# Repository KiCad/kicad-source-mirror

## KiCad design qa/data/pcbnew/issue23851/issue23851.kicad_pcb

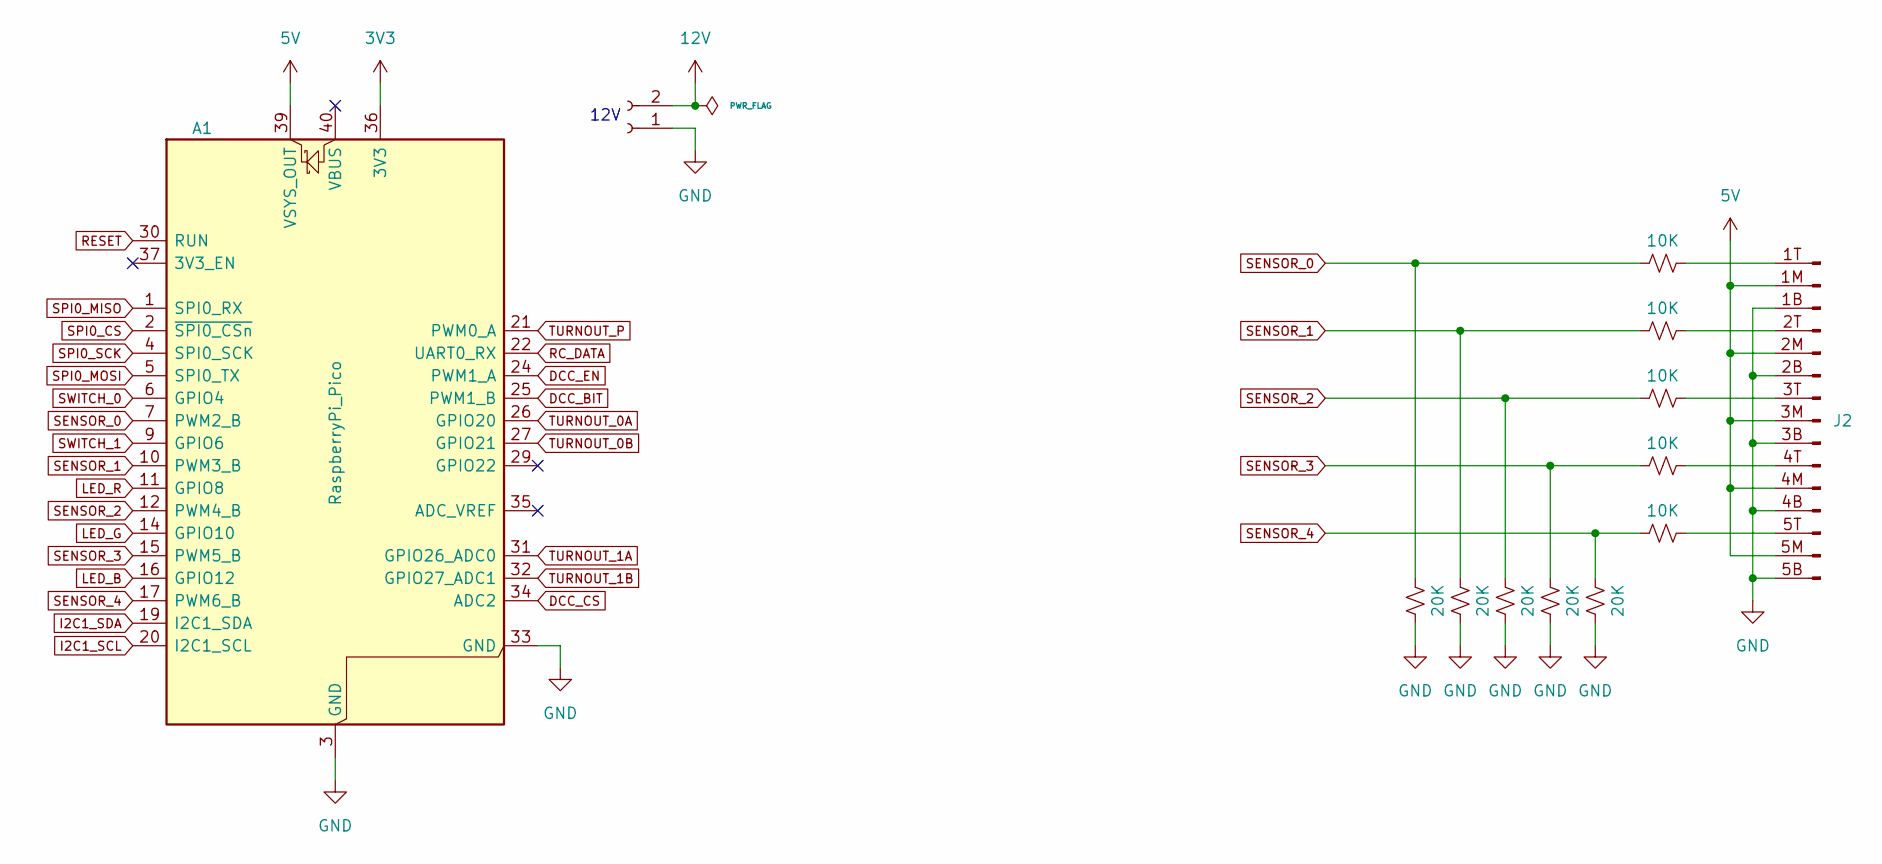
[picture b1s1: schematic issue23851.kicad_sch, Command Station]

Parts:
A1: RaspberryPi_Pico; RaspberryPi_Pico_Common_HDR
J1: Conn_01x02_Socket; PinSocket_1x02_P2.54mm_Vertical
J2: Conn_03x05_Pin; PinHeader_3x05_P2.54mm_Horizontal
R1, R2, R3, R4, R5: 10K; R_Axial_DIN0204_L3.6mm_D1.6mm_P7.62mm_Horizontal
R6, R7, R8, R9, R10: 20K; R_Axial_DIN0204_L3.6mm_D1.6mm_P7.62mm_Horizontal

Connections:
3V3: A1.36 (3V3)
5V: A1.39 (VSYS_OUT), J2.1M, J2.2M, J2.3M, J2.4M, J2.5M
12V: J1.2
DCC_BIT: A1.25 (PWM1_B)
DCC_CS: A1.34 (ADC2)
DCC_EN: A1.24 (PWM1_A)
GND: A1.3 (GND), A1.8 (GND), A1.13 (GND), A1.18 (GND), A1.23 (GND), A1.28 (GND), A1.33 (GND), A1.38 (GND), J1.1, J2.1B, J2.2B, J2.3B, J2.4B, J2.5B, R6.2, R7.2, R8.2, R9.2, R10.2
I2C1_SCL: A1.20 (I2C1_SCL)
I2C1_SDA: A1.19 (I2C1_SDA)
LED_B: A1.16 (GPIO12)
LED_G: A1.14 (GPIO10)
LED_R: A1.11 (GPIO8)
unnamed: J2.1T, R1.2
unnamed: J2.2T, R2.2
unnamed: J2.3T, R3.2
unnamed: J2.4T, R4.2
unnamed: J2.5T, R5.2
RC_DATA: A1.22 (UART0_RX)
RESET: A1.30 (RUN)
SENSOR_0: A1.7 (PWM2_B), R1.1, R10.1
SENSOR_1: A1.10 (PWM3_B), R2.1, R9.1
SENSOR_2: A1.12 (PWM4_B), R3.1, R8.1
SENSOR_3: A1.15 (PWM5_B), R4.1, R7.1
SENSOR_4: A1.17 (PWM6_B), R5.1, R6.1
SPI0_CS: A1.2 (~SPI0_CSn)
SPI0_MISO: A1.1 (SPI0_RX)
SPI0_MOSI: A1.5 (SPI0_TX)
SPI0_SCK: A1.4 (SPI0_SCK)
SWITCH_0: A1.6 (GPIO4)
SWITCH_1: A1.9 (GPIO6)
TURNOUT_0A: A1.26 (GPIO20)
TURNOUT_0B: A1.27 (GPIO21)
TURNOUT_1A: A1.31 (GPIO26_ADC0)
TURNOUT_1B: A1.32 (GPIO27_ADC1)
TURNOUT_P: A1.21 (PWM0_A)

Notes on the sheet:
12V

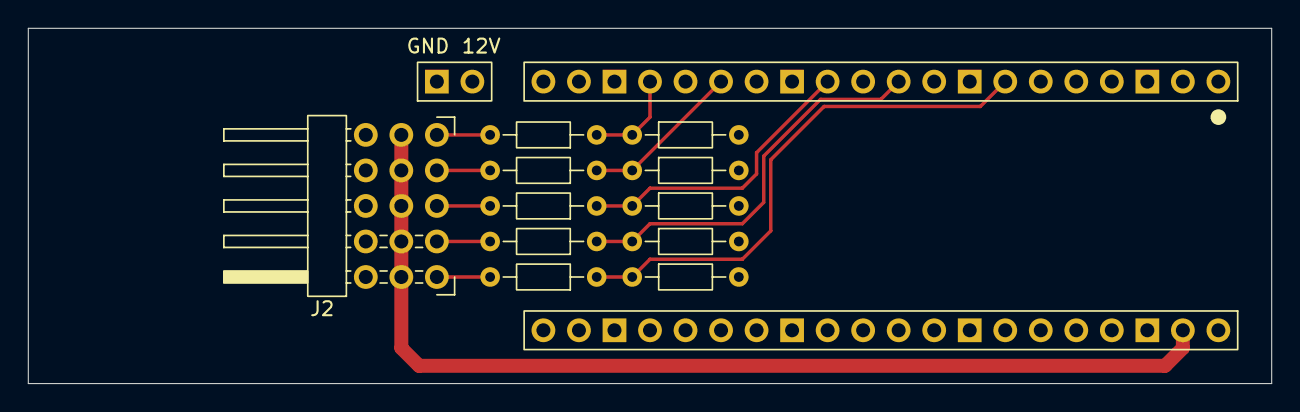
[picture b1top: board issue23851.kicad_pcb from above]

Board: 2 copper layers, 88.9 x 25.4 mm, 13 parts (0 on the bottom side), 12 nets.

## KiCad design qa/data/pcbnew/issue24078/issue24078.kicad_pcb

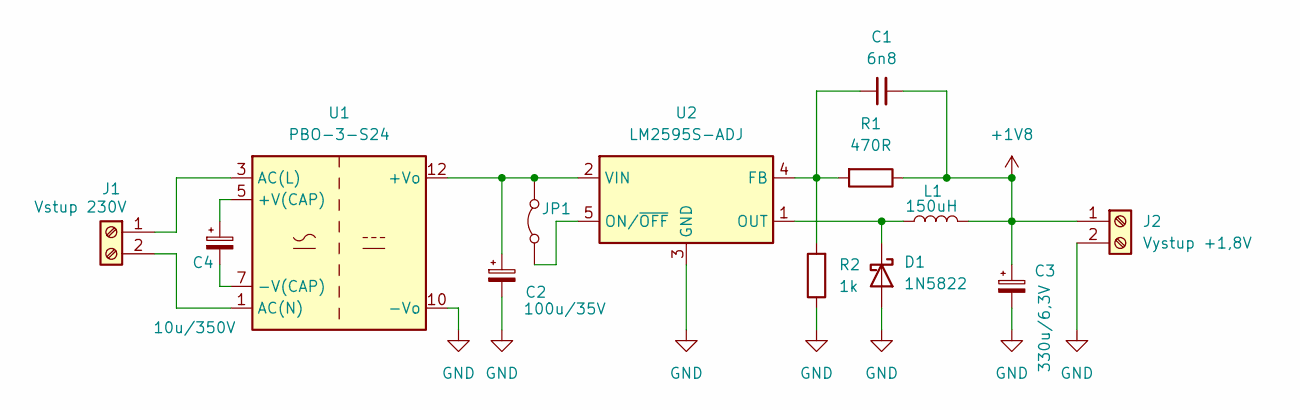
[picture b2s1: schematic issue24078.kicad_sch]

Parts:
C1: 6n8; C_1206_3216Metric_Pad1.33x1.80mm_HandSolder
C2: 100u/35V; CP_Radial_D8.0mm_P3.50mm
C3: 330u/6,3V; CP_Radial_D6.3mm_P2.50mm
C4: 10u/350V; CP_Radial_D8.0mm_P3.50mm
D1: 1N5822; D_DO-201AD_P15.24mm_Horizontal
J1: Vstup 230V; Altech_AK100_1x02_P5.00mm
J2: Vystup +1,8V; Altech_AK100_1x02_P5.00mm
JP1: Jumper_2_Bridged; TestPoint_2Pads_Pitch2.54mm_Drill0.8mm
L1: 150uH; L_Radial_D12.0mm_P10.00mm_Neosid_SD12_style1
R1: 470R; R_1206_3216Metric_Pad1.30x1.75mm_HandSolder
R2: 1k; R_1206_3216Metric_Pad1.30x1.75mm_HandSolder
U1: PBO-3-S24; Converter_ACDC_CUI_PBO-3-Sxx_THT_Vertical
U2: LM2595S-ADJ; TO-263-5_TabPin3

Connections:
+1V8: C1.2, C3.1, J2.1, L1.2, R1.1
GND: C2.2, C3.2, D1.2 (A), J2.2, R2.1, U1.10 (-Vo), U2.3 (GND)
unnamed: D1.1 (K), L1.1, U2.1 (OUT)
unnamed: J1.1, U1.3 (AC(L))
unnamed: J1.2, U1.1 (AC(N))
unnamed: JP1.1 (A), U2.5 (ON/~OFF)
unnamed: C2.1, JP1.2 (B), U1.12 (+Vo), U2.2 (VIN)
unnamed: C4.1, U1.5 (+V(CAP))
unnamed: C4.2, U1.7 (-V(CAP))
unnamed: C1.1, R1.2, R2.2, U2.4 (FB)

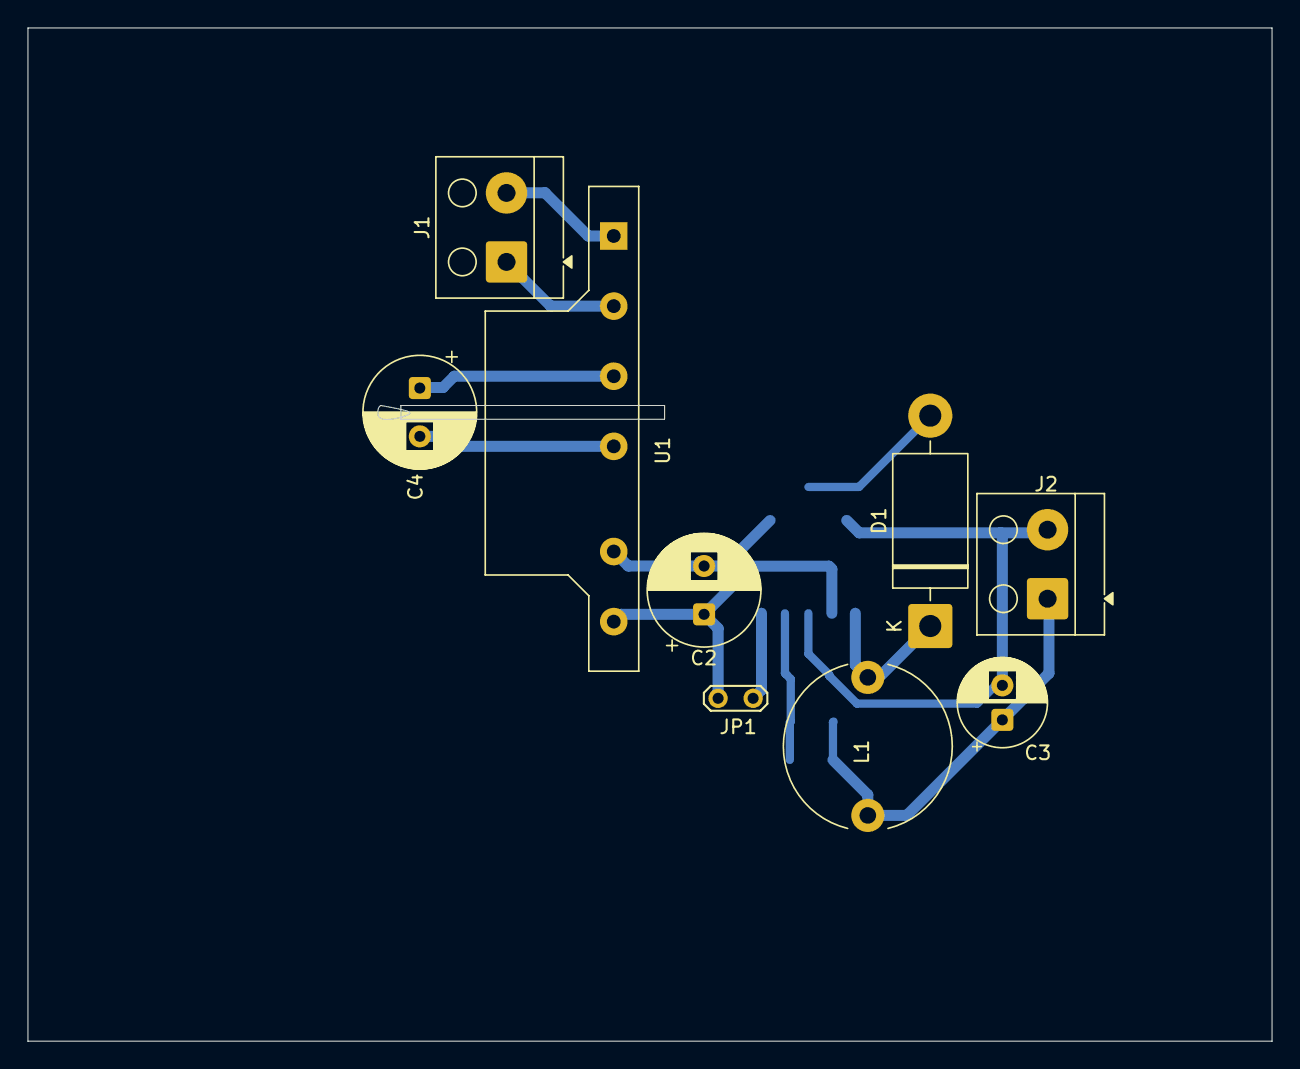
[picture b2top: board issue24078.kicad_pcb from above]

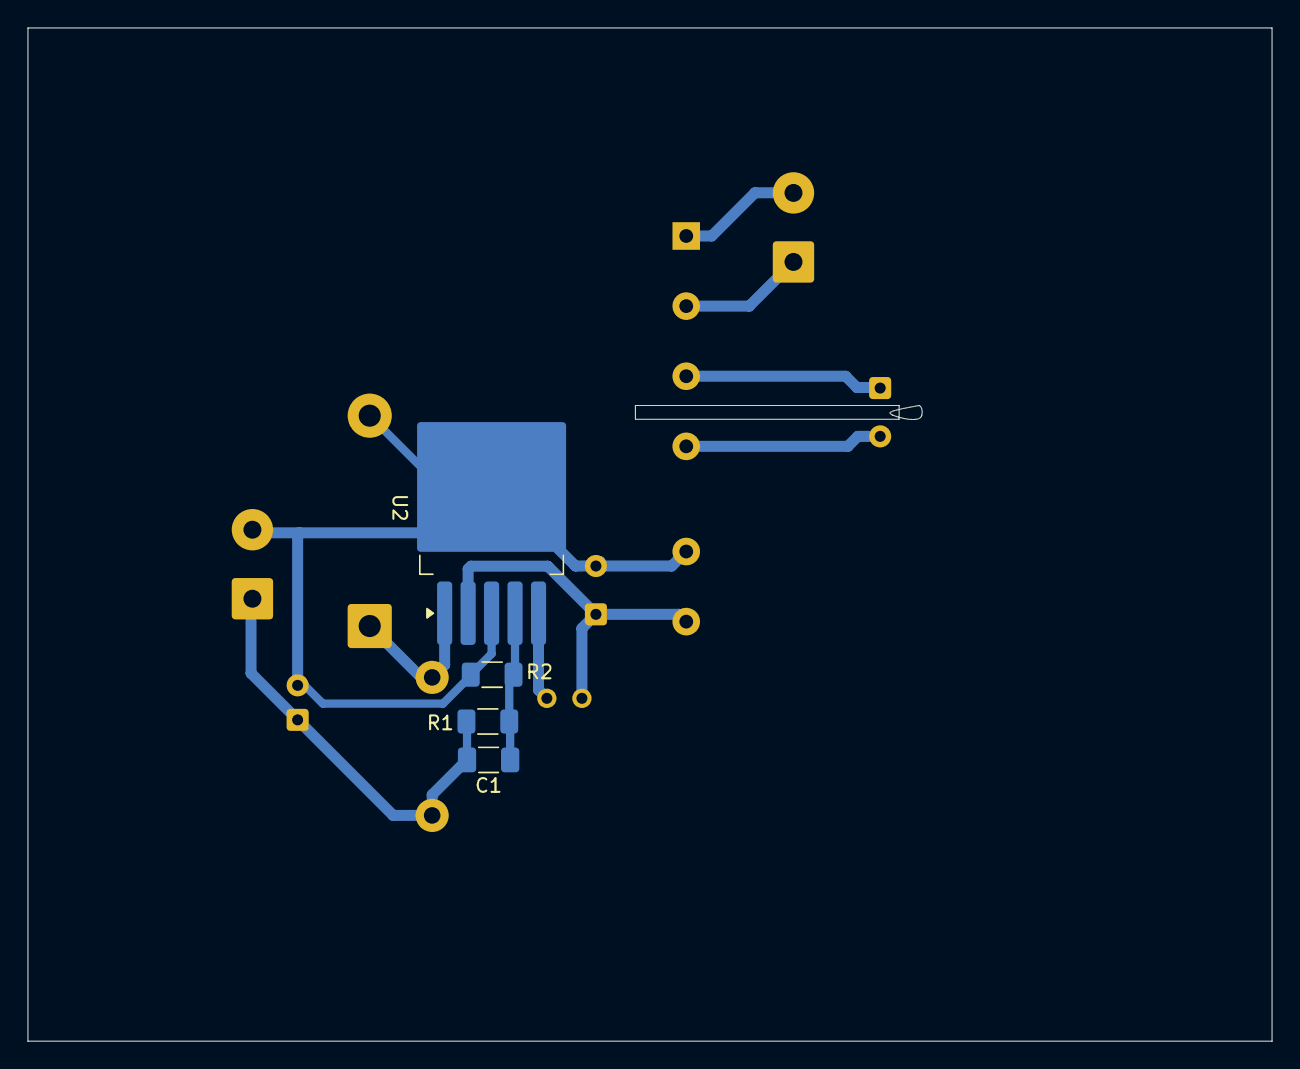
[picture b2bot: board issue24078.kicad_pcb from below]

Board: 2 copper layers, 90.1 x 73.4 mm, 13 parts (4 on the bottom side), 10 nets.

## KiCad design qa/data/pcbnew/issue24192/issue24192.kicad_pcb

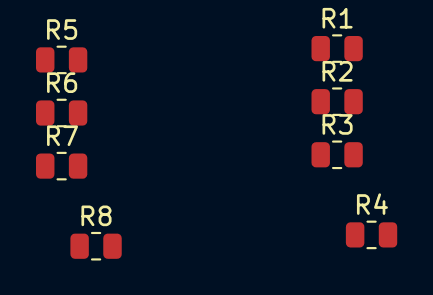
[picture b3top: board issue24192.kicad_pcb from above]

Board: 2 copper layers, 8 parts (0 on the bottom side), 6 nets, no tracks yet.

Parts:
R1, R2, R3, R4, R5, R6, R7, R8: R; R_0805_2012Metric

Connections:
/Untitled Sheet/a: R3.1, R4.2
/Untitled Sheet/x: R1.1, R2.2
unnamed: R1.2, R2.1
unnamed: R3.2, R4.1
unnamed: R5.2, R6.1
unnamed: R7.2, R8.1
